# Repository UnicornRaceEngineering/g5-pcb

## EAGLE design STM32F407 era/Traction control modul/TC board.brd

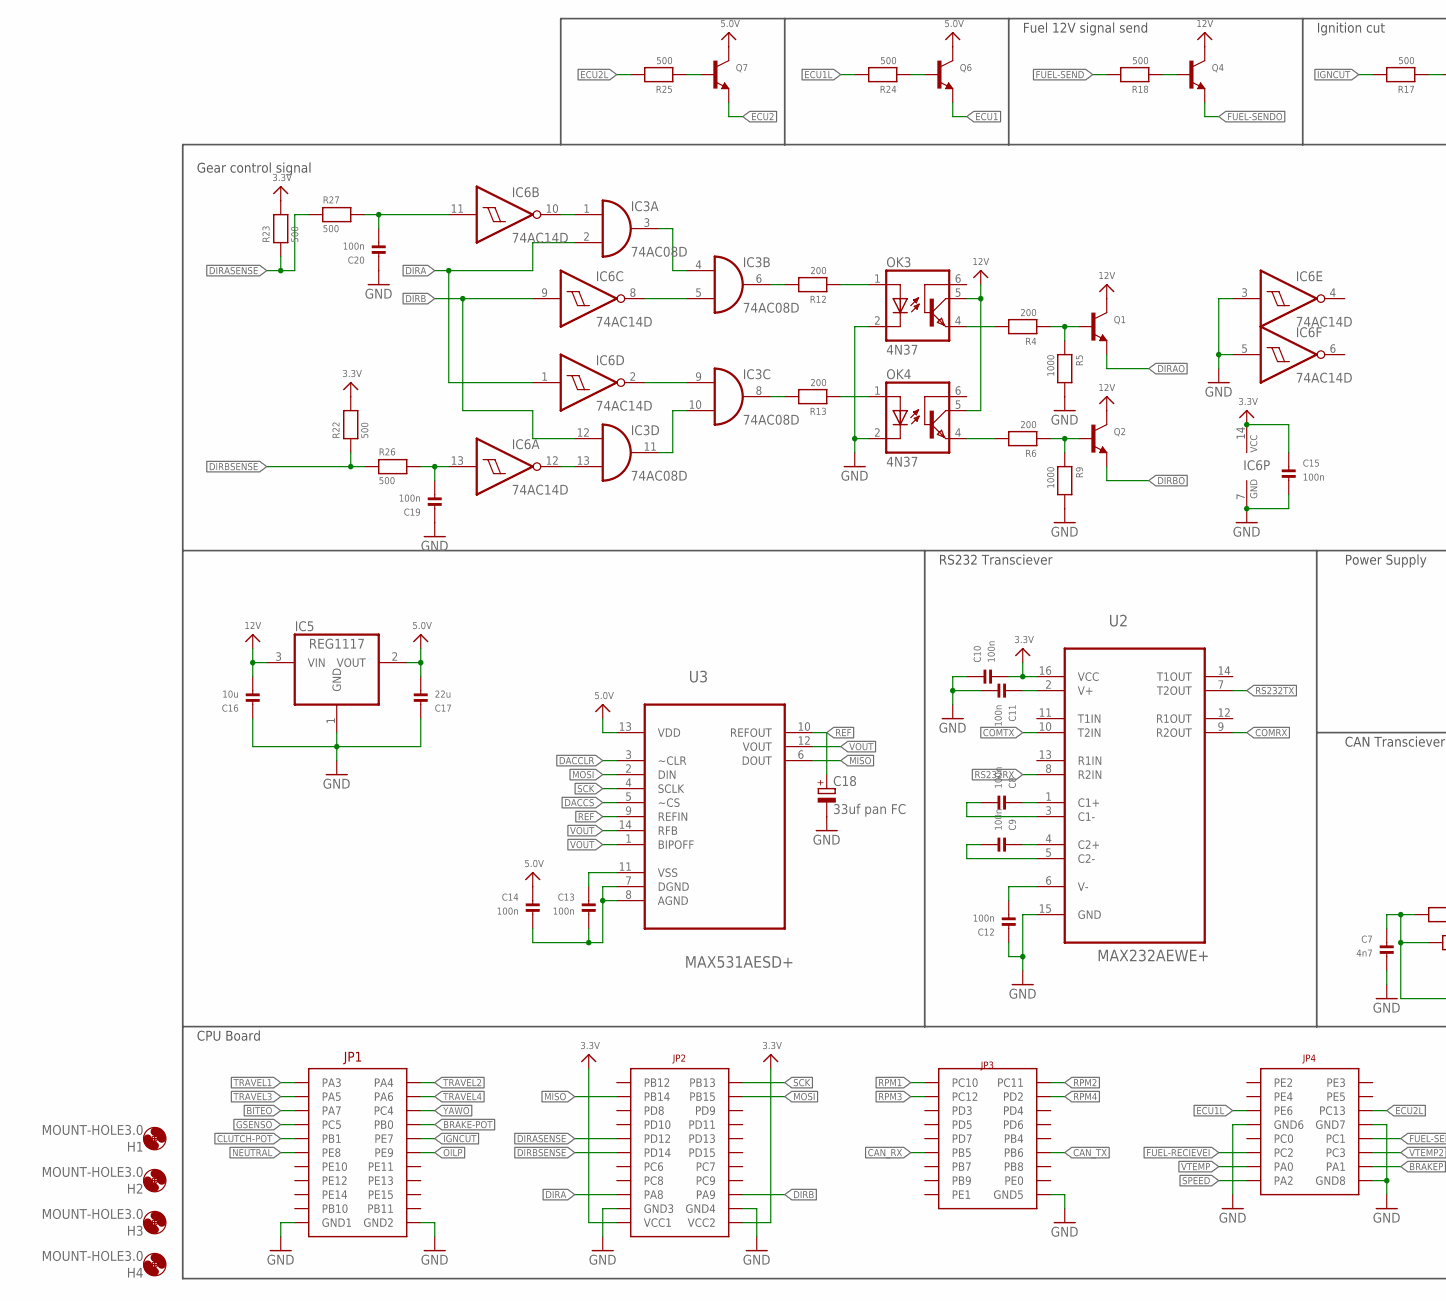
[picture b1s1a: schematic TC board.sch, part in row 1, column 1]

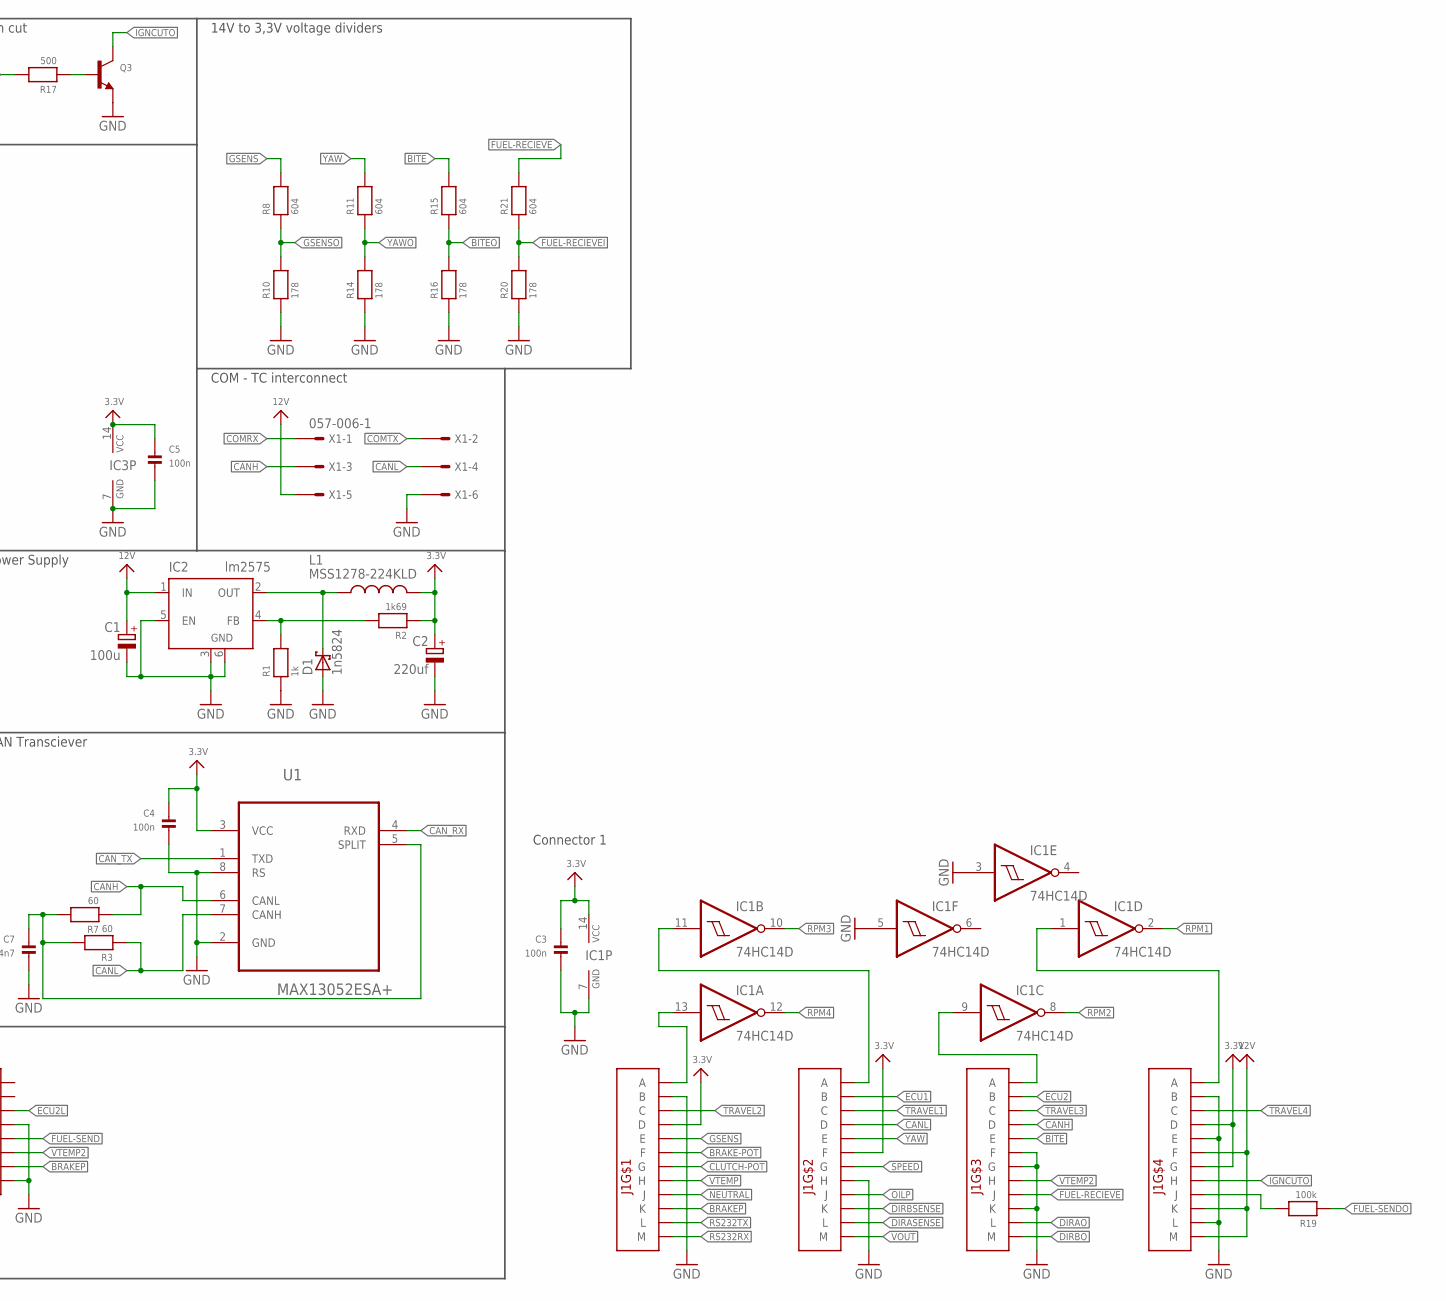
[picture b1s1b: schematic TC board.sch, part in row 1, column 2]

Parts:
C1: 100u; E2,5-7
C2: 220uf; E3,5-8
C3, C4, C5, C8, C9, C10, C11, C12, C13, C14, C15: 100n; _0603
C7: 4n7; _0603
C16: 10u; _0805
C17: 22u; _0805
C18: 33uf pan FC; UD-5X5,8_NICHICON
C19, C20: 100n; _0805
D1: 1n5824; F126Z12
H1, H2, H3, H4: MOUNT-HOLE3.0; 3,0
IC1: 74HC14D; SO14
IC2: lm2575; TO263-5
IC3: 74AC08D; SO14
IC5: REG1117; SOT223
IC6: 74AC14D; SO14
J1: CON1; AUTOCONNECTOR
L1: MSS1278-224KLD; CDRH125
OK3, OK4: 4N37; DIL06
Q1, Q2, Q3, Q4, Q6, Q7: TRANSISTOR_NPNWIDE; SOT23-WIDE
R1: 1k; _0603
R2: 1k69; _0603
R3, R7: 60; _0603
R4, R6, R12, R13: 200; _0603
R5, R9: 1000; _0603
R8, R11, R15, R21: 604; _0603
R10, R14, R16, R20: 178; _0603
R17, R18, R22, R23, R24, R25, R26, R27: 500; _0603
R19: 100k; _0603
U1: MAX13052ESA+; SOIC127P600X175-8N
U2: MAX232AEWE+; SOIC127P1032X265-16N
U3: MAX531AESD+; SOIC127P600X175-14N
U$1: CPU-BOARD; CPU-BOARD-JP1
X1: 057-006-1

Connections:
3.3V: C2.+, C3.1, C4.1, C5.1, C10.2, C15.1, IC1.14 (VCC), IC3.14 (VCC), IC6.14 (VCC), J1.D1 (D), J1.D4 (D), J1.F2 (F), J1.G4 (G), L1.2, R2.1, R22.2, R23.2, U1.3 (VCC), U2.16 (VCC), U$1.P$43 (VCC1), U$1.P$44 (VCC2)
5.0V: C14.1, C17.2, IC5.2 (VOUT), Q6.3 (C), Q7.3 (C), U3.13 (VDD)
12V: C1.+, C16.2, IC2.1 (IN), IC5.3 (VIN), J1.F4 (F), J1.K4 (K), J1.M4 (M), OK3.5 (COL), OK4.5 (COL), Q1.3 (C), Q2.3 (C), Q4.3 (C), X1.5
BITE: J1.E3 (E), R15.2
BITEO: R15.1, R16.2, U$1.P$5 (PA7)
BRAKE-POT: J1.F1 (F), U$1.P$8 (PB0)
BRAKEP: J1.K1 (K), U$1.P$76 (PA1)
CANH: J1.D3 (D), R7.1, U1.6 (CANL), X1.3
CANL: J1.D2 (D), R3.1, U1.7 (CANH), X1.4
CAN_RX: U1.4 (RXD), U$1.P$55 (PB5)
CAN_TX: U1.1 (TXD), U$1.P$56 (PB6)
CLUTCH-POT: J1.G1 (G), U$1.P$9 (PB1)
COMRX: U2.9 (R2OUT), X1.1
COMTX: U2.10 (T2IN), X1.2
DACCLR: U3.3 (~CLR)
DACCS: U3.5 (~CS)
DIRA: IC3.2 (I1), IC6.1 (I), U$1.P$39 (PA8)
DIRAO: J1.L3 (L), Q1.2 (E)
DIRASENSE: J1.L2 (L), R23.1, R27.1, U$1.P$31 (PD12)
DIRB: IC3.12 (I0), IC6.9 (I), U$1.P$40 (PA9)
DIRBO: J1.M3 (M), Q2.2 (E)
DIRBSENSE: J1.K2 (K), R22.1, R26.1, U$1.P$33 (PD14)
ECU1: J1.B2 (B), Q6.2 (E)
ECU1L: R24.2, U$1.P$67 (PE6)
ECU2: J1.B3 (B), Q7.2 (E)
ECU2L: R25.2, U$1.P$68 (PC13)
FUEL-RECIEVE: J1.J3 (J), R21.2
FUEL-RECIEVEI: R20.2, R21.1, U$1.P$73 (PC2)
FUEL-SEND: R18.2, U$1.P$72 (PC1)
FUEL-SENDO: Q4.2 (E), R19.1
GND: C1.-, C2.-, C3.2, C4.2, C5.2, C7.2, C10.1, C11.2, C12.1, C15.2, C16.1, C17.1, C18.-, C19.1, C20.1, D1.A, IC1.3 (I), IC1.5 (I), IC1.7 (GND), IC2.3 (GND), IC2.5 (EN), IC2.6 (GND), IC3.7 (GND), IC5.1 (GND), IC6.3 (I), IC6.5 (I), IC6.7 (GND), J1.B1 (B), J1.B4 (B), J1.E4 (E), J1.F3 (F), J1.G3 (G), J1.H2 (H), J1.K3 (K), J1.L4 (L), OK3.2 (C), OK4.2 (C), Q3.2 (E), R1.1, R5.2, R9.2, R10.1, R14.1, R16.1, R20.1, U1.2 (GND), U1.8 (RS), U2.15 (GND), U$1.P$19 (GND1), U$1.P$20 (GND2), U$1.P$41 (GND3), U$1.P$42 (GND4), U$1.P$62 (GND5), U$1.P$69 (GND6), U$1.P$70 (GND7), U$1.P$78 (GND8), X1.6
GSENS: J1.E1 (E), R8.2
GSENSO: R8.1, R10.2, U$1.P$7 (PC5)
IGNCUT: R17.2, U$1.P$10 (PE7)
IGNCUTO: J1.H4 (H), Q3.3 (C)
MISO: U3.6 (DOUT), U$1.P$25 (PB14)
MOSI: U3.2 (DIN), U$1.P$26 (PB15)
unnamed: IC2.4 (FB), R1.2, R2.2
unnamed: D1.C, IC2.2 (OUT), L1.1
unnamed: IC1.9 (I), J1.A3 (A)
unnamed: IC1.13 (I), J1.A1 (A)
unnamed: IC1.1 (I), J1.A4 (A)
unnamed: IC1.11 (I), J1.A2 (A)
unnamed: OK3.4 (EMI), R4.2
unnamed: Q1.1 (B), R4.1, R5.1
unnamed: OK4.4 (EMI), R6.2
unnamed: Q2.1 (B), R6.1, R9.1
unnamed: IC3.8 (O), R13.2
unnamed: C7.1, R3.2, R7.2, U1.5 (SPLIT)
unnamed: C12.2, U2.6 (V-)
unnamed: C9.1, U2.4 (C2+)
unnamed: IC3.9 (I0), IC6.2 (O)
unnamed: IC3.5 (I1), IC6.8 (O)
unnamed: OK4.1 (A), R13.1
unnamed: OK3.1 (A), R12.1
unnamed: IC3.6 (O), R12.2
unnamed: C9.2, U2.5 (C2-)
unnamed: C8.2, U2.3 (C1-)
unnamed: C8.1, U2.1 (C1+)
unnamed: C11.1, U2.2 (V+)
unnamed: Q3.1 (B), R17.1
unnamed: J1.J4 (J), R19.2
unnamed: Q4.1 (B), R18.1
unnamed: C13.2, C14.2, U3.7 (DGND), U3.8 (AGND)
unnamed: C13.1, U3.11 (VSS)
unnamed: IC3.3 (O), IC3.4 (I0)
unnamed: IC3.10 (I1), IC3.11 (O)
unnamed: IC3.13 (I1), IC6.12 (O)
unnamed: IC3.1 (I0), IC6.10 (O)
unnamed: C20.2, IC6.11 (I), R27.2
unnamed: Q6.1 (B), R24.1
unnamed: Q7.1 (B), R25.1
unnamed: C19.2, IC6.13 (I), R26.2
NEUTRAL: J1.J1 (J), U$1.P$11 (PE8)
OILP: J1.J2 (J), U$1.P$12 (PE9)
REF: C18.+, U3.9 (REFIN), U3.10 (REFOUT)
RPM1: IC1.2 (O), U$1.P$45 (PC10)
RPM2: IC1.8 (O), U$1.P$46 (PC11)
RPM3: IC1.10 (O), U$1.P$47 (PC12)
RPM4: IC1.12 (O), U$1.P$48 (PD2)
RS232RX: J1.M1 (M), U2.8 (R2IN)
RS232TX: J1.L1 (L), U2.7 (T2OUT)
SCK: U3.4 (SCLK), U$1.P$24 (PB13)
SPEED: J1.G2 (G), U$1.P$77 (PA2)
TRAVEL1: J1.C2 (C), U$1.P$1 (PA3)
TRAVEL2: J1.C1 (C), U$1.P$2 (PA4)
TRAVEL3: J1.C3 (C), U$1.P$3 (PA5)
TRAVEL4: J1.C4 (C), U$1.P$4 (PA6)
VOUT: J1.M2 (M), U3.1 (BIPOFF), U3.12 (VOUT), U3.14 (RFB)
VTEMP: J1.H1 (H), U$1.P$75 (PA0)
VTEMP2: J1.H3 (H), U$1.P$74 (PC3)
YAW: J1.E2 (E), R11.2
YAWO: R11.1, R14.2, U$1.P$6 (PC4)

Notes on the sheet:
CPU Board
Connector 1
RS232 Transciever
CAN Transciever
Power Supply
Gear control signal
COM - TC interconnect
14V to 3,3V voltage dividers
Ignition cut
Fuel 12V signal send

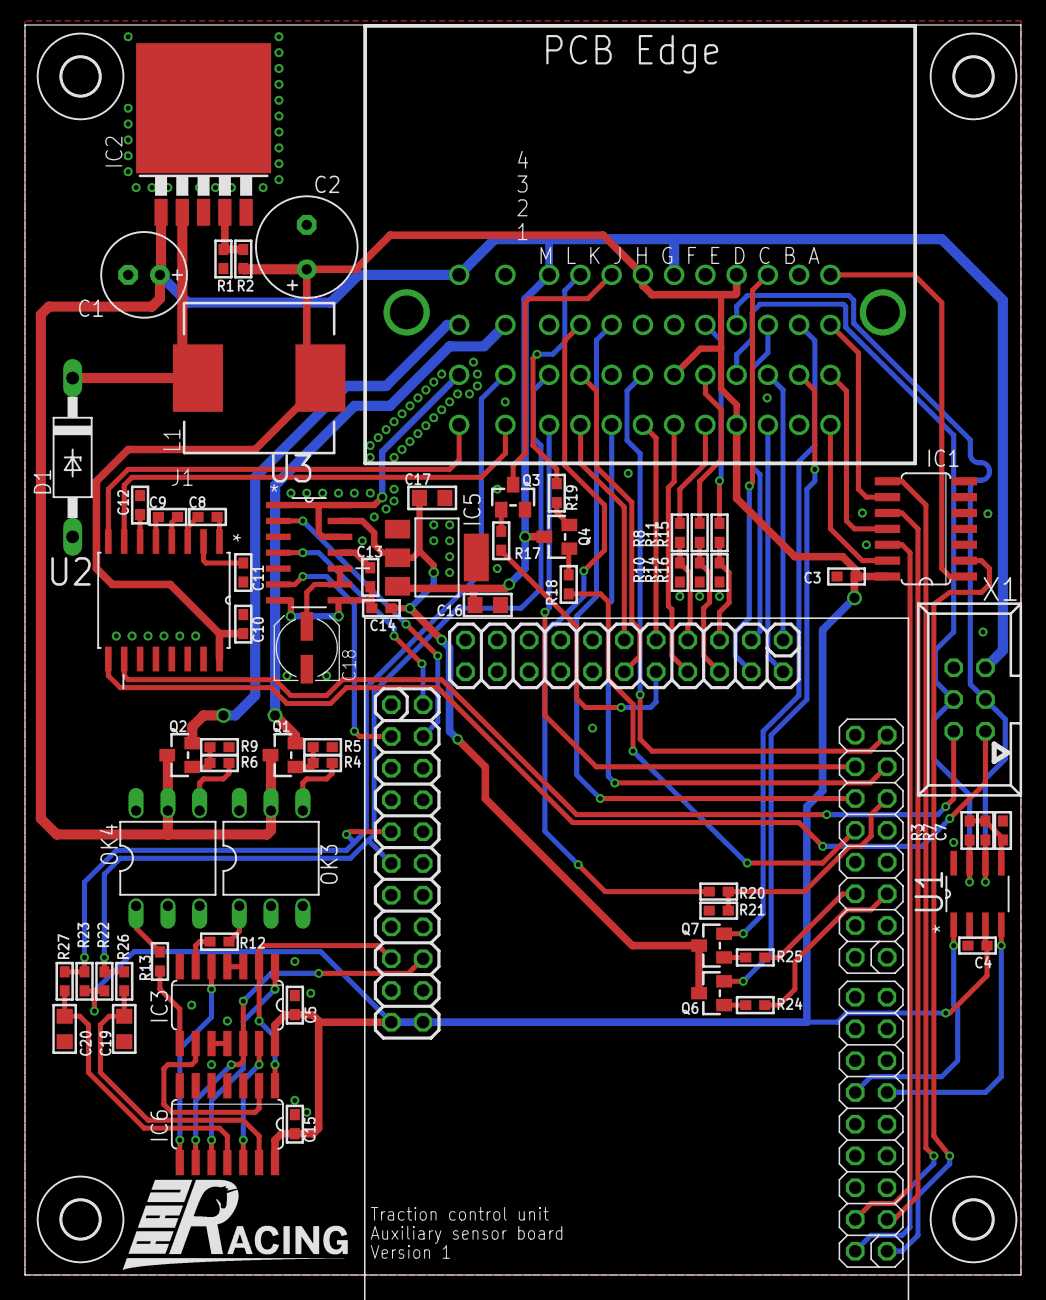
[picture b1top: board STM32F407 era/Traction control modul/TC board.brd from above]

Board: 2 copper layers, 79.7 x 100.0 mm, 71 parts (0 on the bottom side), 91 nets.

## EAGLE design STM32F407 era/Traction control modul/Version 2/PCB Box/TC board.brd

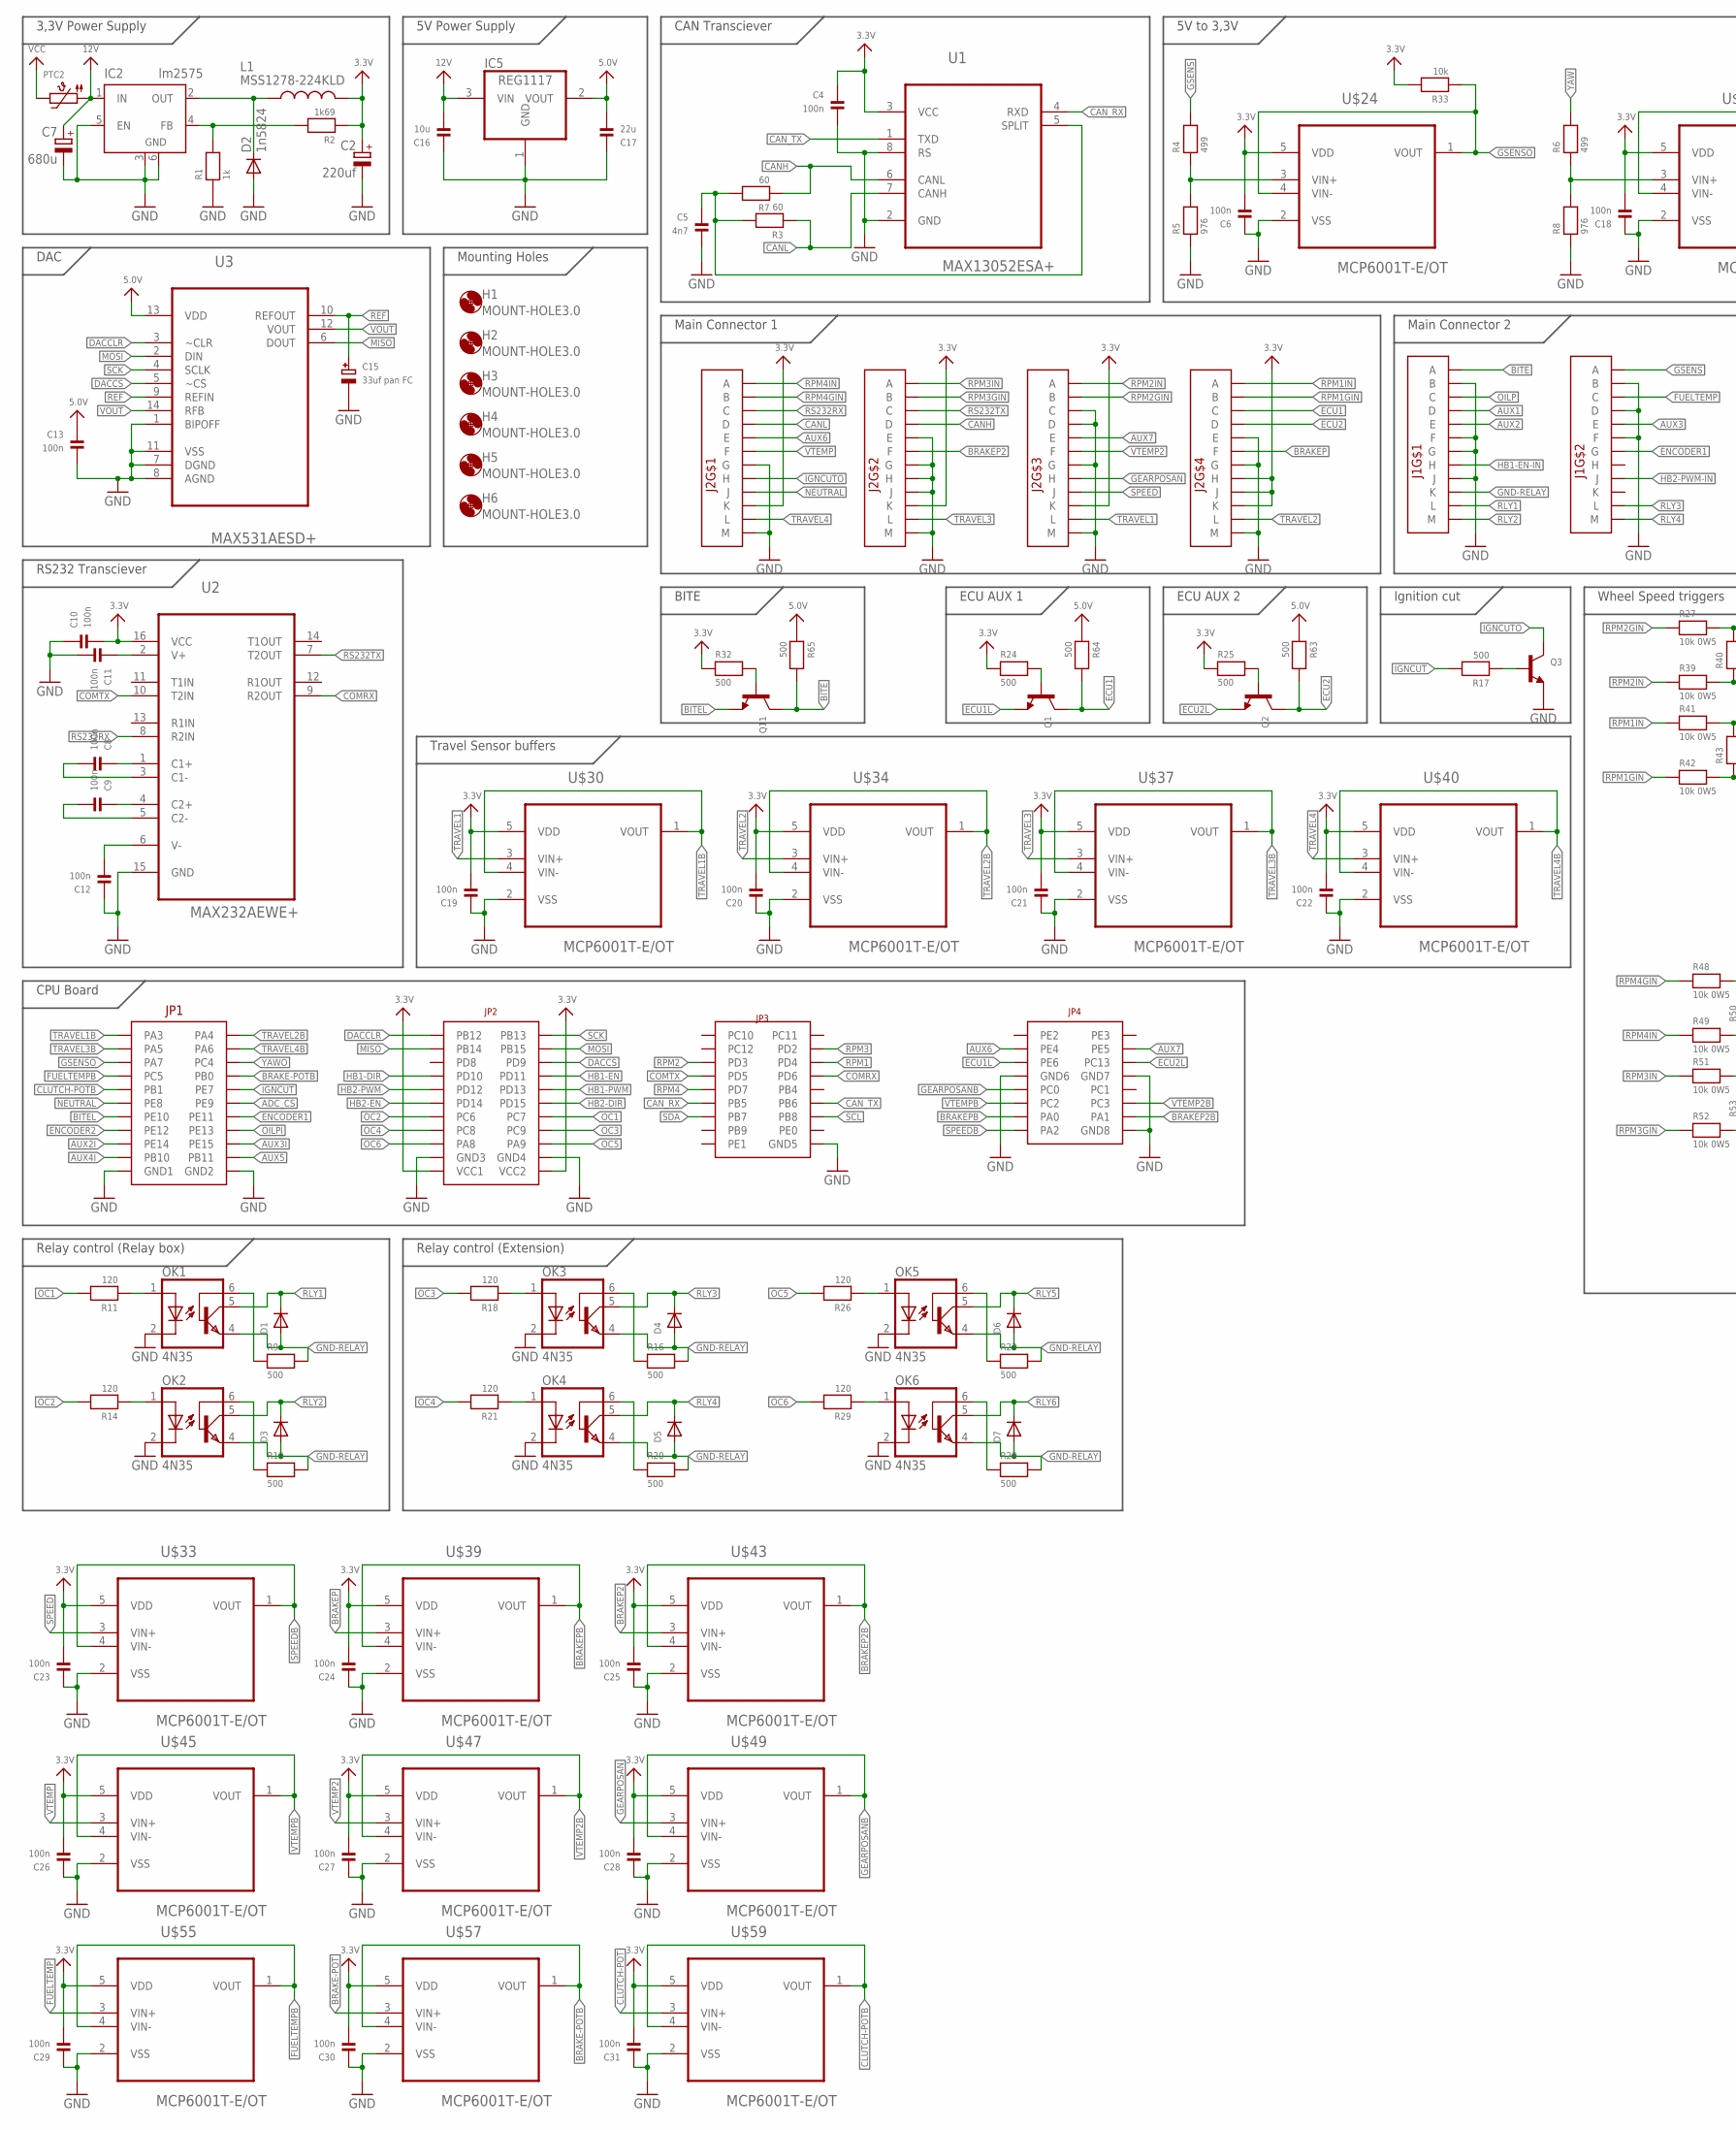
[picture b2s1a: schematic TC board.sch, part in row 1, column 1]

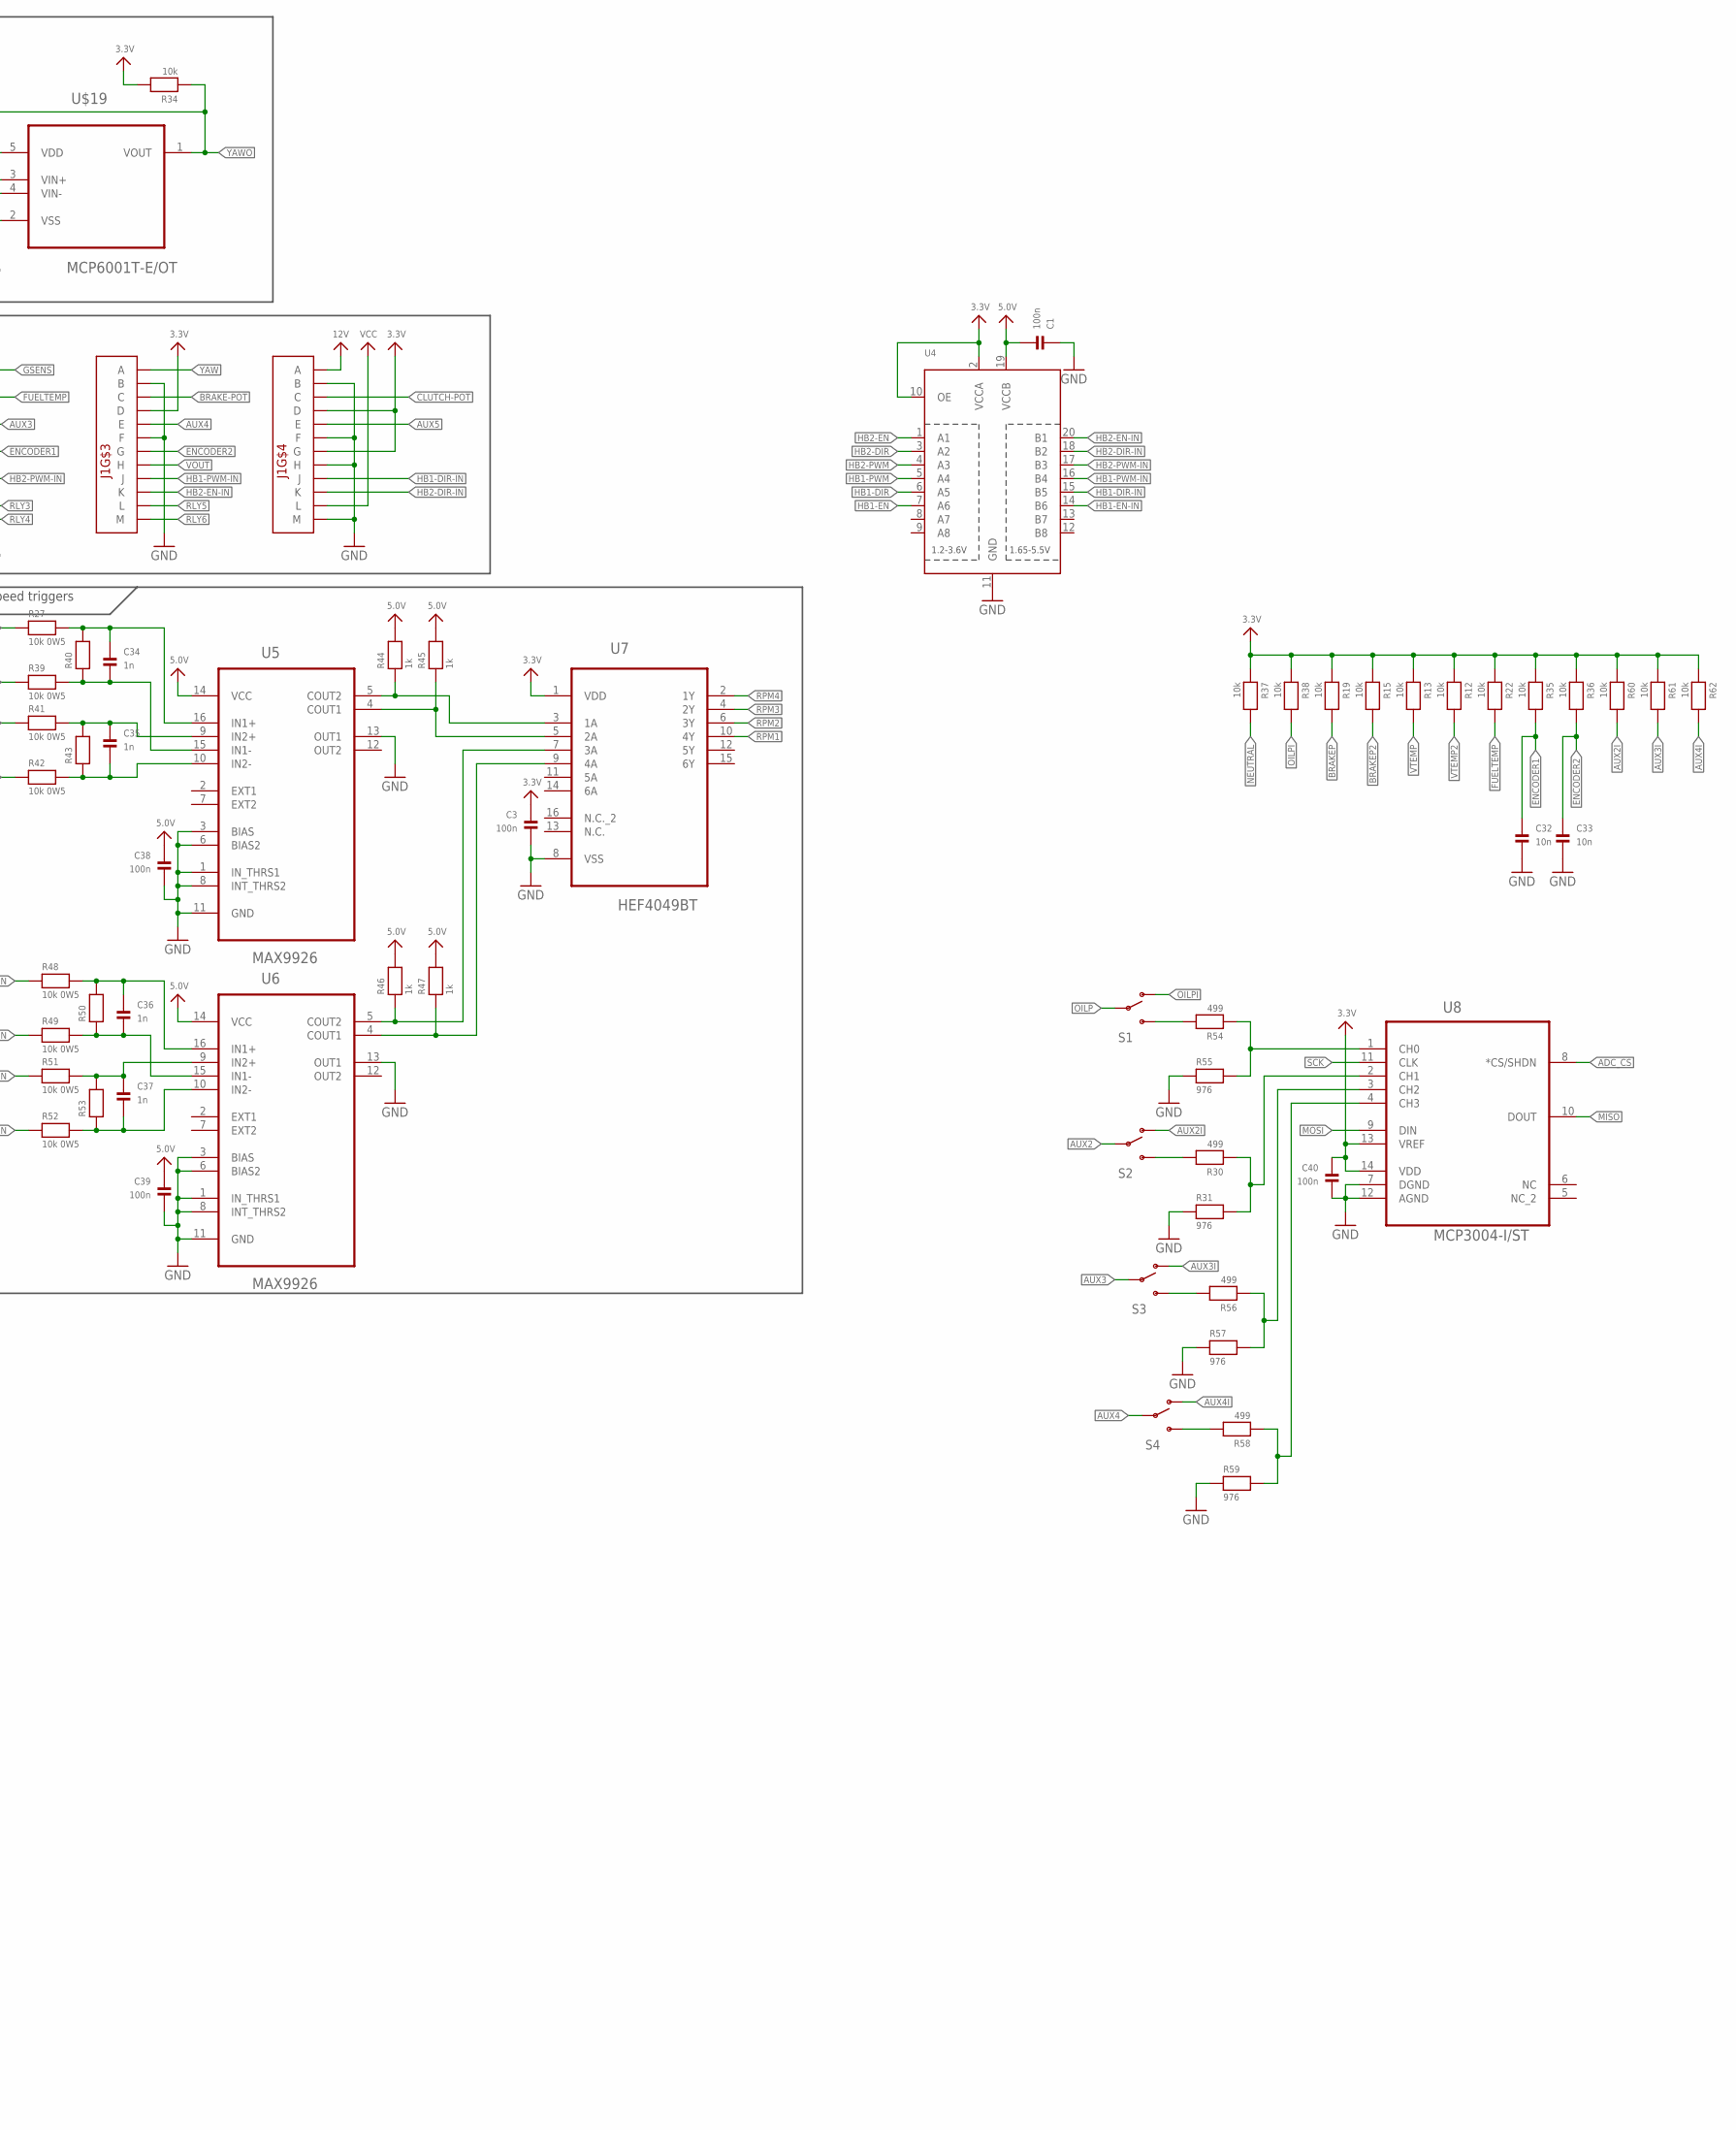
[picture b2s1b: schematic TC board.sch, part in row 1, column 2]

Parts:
C1, C3, C4, C6, C8, C9, C10, C11, C12, C13, C18, C19, C20, C21, C22, C23, C24, C25, C26, C27, C28, C29, C30, C31, C38, C39, C40: 100n; _0603
C2: 220uf; E3,5-8
C5: 4n7; _0603
C7: 680u; E5-10,5
C15: 33uf pan FC; PANASONIC_D
C16: 10u; _0805
C17: 22u; _0805
C32, C33: 10n; _0603
C34, C35, C36, C37: 1n; _0603
D1, D3, D4, D5, D6, D7: DIODESOD-323F; SOD-323F
D2: 1n5824; DO201-15
H1, H2, H3, H4, H5, H6: MOUNT-HOLE3.0; 3,0
IC2: lm2575; TO263-5
IC5: REG1117; SOT223
J1, J2: CON1; AUTOCONNECTOR
L1: MSS1278-224KLD; CDRH125
OK1, OK2, OK3, OK4, OK5, OK6: 4N35; DIL06
PTC2: PTC1812
Q1, Q2, Q3, Q11: TRANSISTOR_NPNWIDE; SOT23-WIDE
R1, R44, R45, R46, R47: 1k; _0603
R2: 1k69; _0603
R3, R7: 60; _0603
R4, R6, R30, R54, R56, R58: 499; _0603
R5, R8, R31, R55, R57, R59: 976; _0603
R9, R10, R16, R17, R20, R23, R24, R25, R28, R32, R63, R64, R65: 500; _0603
R11, R14, R18, R21, R26, R29: 120; _0603
R12, R13, R15, R19, R22, R33, R34, R35, R36, R37, R38, R60, R61, R62: 10k; _0603
R27, R39, R41, R42, R48, R49, R51, R52: 10k 0W5; _0805
R40, R43, R50, R53: RESISTOR_0805; _0805
S1, S2, S3, S4: SWITCH-SPDT-SMD-A; SWITCH-SPST-SMD-A
U1: MAX13052ESA+; SOIC127P600X175-8N
U2: MAX232AEWE+; SOIC127P1032X265-16N
U3: MAX531AESD+; SOIC127P600X175-14N
U4: TXB0108PWR; TSSOP20
U5, U6: MAX9926; SOP63P600X175-16N
U7: HEF4049BT; SOIC127P600X175-16N
U8: MCP3004-I/ST; SOP65P640X120-14N
U$1: CPU-BOARD; CPU-BOARD-JP1
U$19, U$24, U$30, U$33, U$34, U$37, U$39, U$40, U$43, U$45, U$47, U$49, U$55, U$57, U$59: MCP6001T-E/OT; SOT95P270X145-5N

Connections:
3.3V: C2.+, C3.1, C4.1, C6.2, C10.2, C18.2, C19.2, C20.2, C21.2, C22.2, C23.2, C24.2, C25.2, C26.2, C27.2, C28.2, C29.2, C30.2, C31.2, C40.1, J1.D3 (D), J1.D4 (D), J1.G4 (G), J2.H4 (H), J2.J4 (J), J2.K1 (K), J2.K2 (K), J2.K3 (K), J2.K4 (K), L1.2, R2.1, R12.1, R13.1, R15.1, R19.1, R22.1, R24.1, R25.1, R32.1, R33.2, R34.2, R35.1, R36.1, R37.1, R38.1, R60.1, R61.1, R62.1, U1.3 (VCC), U2.16 (VCC), U4.2 (VCCA), U4.10 (OE), U7.1 (VDD), U8.13 (VREF), U8.14 (VDD), U$1.P$43 (VCC1), U$1.P$44 (VCC2), U$19.5 (VDD), U$24.5 (VDD), U$30.5 (VDD), U$33.5 (VDD), U$34.5 (VDD), U$37.5 (VDD), U$39.5 (VDD), U$40.5 (VDD), U$43.5 (VDD), U$45.5 (VDD), U$47.5 (VDD), U$49.5 (VDD), U$55.5 (VDD), U$57.5 (VDD), U$59.5 (VDD)
5.0V: C1.2, C13.1, C17.2, C38.1, C39.1, IC5.2 (VOUT), R44.2, R45.2, R46.2, R47.2, R63.1, R64.1, R65.1, U3.13 (VDD), U4.19 (VCCB), U5.14 (VCC), U6.14 (VCC); also elsewhere on the board
12V: C7.+, C16.2, IC2.1 (IN), IC5.3 (VIN), J1.A4 (A), PTC2.P$1 (1)
ADC_CS: U8.8 (*CS/SHDN), U$1.P$12 (PE9)
AUX1: J1.D1 (D)
AUX2: J1.E1 (E), S2.2
AUX2I: R60.2, S2.1 (O), U$1.P$17 (PE14)
AUX3: J1.E2 (E), S3.2
AUX3I: R61.2, S3.1 (O), U$1.P$18 (PE15)
AUX4: J1.E3 (E), S4.2
AUX4I: R62.2, S4.1 (O), U$1.P$21 (PB10)
AUX5: J1.E4 (E), U$1.P$22 (PB11)
AUX6: J2.E1 (E), U$1.P$65 (PE4)
AUX7: J2.E3 (E), U$1.P$66 (PE5)
BITE: J1.A1 (A), Q11.3 (C), R65.2
BITEL: Q11.2 (E), U$1.P$13 (PE10)
BRAKE-POT: J1.C3 (C), U$57.3 (VIN+)
BRAKE-POTB: U$1.P$8 (PB0), U$57.1 (VOUT), U$57.4 (VIN-)
BRAKEP: J2.F4 (F), R19.2, U$39.3 (VIN+)
BRAKEP2: J2.F2 (F), R15.2, U$43.3 (VIN+)
BRAKEP2B: U$1.P$76 (PA1), U$43.1 (VOUT), U$43.4 (VIN-)
BRAKEPB: U$1.P$75 (PA0), U$39.1 (VOUT), U$39.4 (VIN-)
CANH: J2.D2 (D), R7.1, U1.6 (CANL)
CANL: J2.D1 (D), R3.1, U1.7 (CANH)
CAN_RX: U1.4 (RXD), U$1.P$55 (PB5)
CAN_TX: U1.1 (TXD), U$1.P$56 (PB6)
CLUTCH-POT: J1.C4 (C), U$59.3 (VIN+)
CLUTCH-POTB: U$1.P$9 (PB1), U$59.1 (VOUT), U$59.4 (VIN-)
COMRX: U2.9 (R2OUT), U$1.P$52 (PD6)
COMTX: U2.10 (T2IN), U$1.P$51 (PD5)
DACCLR: U3.3 (~CLR), U$1.P$23 (PB12); also elsewhere on the board
DACCS: U3.5 (~CS), U$1.P$28 (PD9); also elsewhere on the board
ECU1: J2.C4 (C), Q1.3 (C), R64.2
ECU1L: Q1.2 (E), U$1.P$67 (PE6)
ECU2: J2.D4 (D), Q2.3 (C), R63.2
ECU2L: Q2.2 (E), U$1.P$68 (PC13)
ENCODER1: C32.1, J1.G2 (G), R35.2, U$1.P$14 (PE11)
ENCODER2: C33.1, J1.G3 (G), R36.2, U$1.P$15 (PE12)
FUELTEMP: J1.C2 (C), R22.2, U$55.3 (VIN+)
FUELTEMPB: U$1.P$7 (PC5), U$55.1 (VOUT), U$55.4 (VIN-)
GEARPOSAN: J2.H3 (H), U$49.3 (VIN+)
GEARPOSANB: U$1.P$71 (PC0), U$49.1 (VOUT), U$49.4 (VIN-)
GND: C1.1, C2.-, C3.2, C4.2, C5.2, C6.1, C7.-, C10.1, C11.2, C12.1, C13.2, C15.-, C16.1, C17.1, C18.1, C19.1, C20.1, C21.1, C22.1, C23.1, C24.1, C25.1, C26.1, C27.1, C28.1, C29.1, C30.1, C31.1, C32.2, C33.2, C38.2, C39.2, C40.2, D2.A, IC2.3 (GND), IC2.5 (EN), IC2.6 (GND), IC5.1 (GND), J1.B1 (B), J1.B2 (B), J1.B3 (B), J1.B4 (B), J1.D2 (D), J1.F1 (F), J1.F2 (F), J1.F3 (F), J1.F4 (F), J1.G1 (G), J1.H4 (H), J1.J1 (J), J1.M4 (M), J2.C3 (C), J2.D3 (D), J2.E2 (E), J2.E4 (E), J2.G1 (G), J2.G2 (G), J2.G3 (G), J2.G4 (G), J2.H2 (H), J2.J2 (J), J2.M1 (M), J2.M2 (M), J2.M3 (M), J2.M4 (M), OK1.2 (C), OK2.2 (C), OK3.2 (C), OK4.2 (C), OK5.2 (C), OK6.2 (C), Q3.2 (E), R1.1, R5.1, R8.1, R31.1, R55.1, R57.1, R59.1, U1.2 (GND), U1.8 (RS), U2.15 (GND), U3.1 (BIPOFF), U3.7 (DGND), U3.8 (AGND), U3.11 (VSS), U4.11 (GND), U5.1 (IN_THRS1), U5.3 (BIAS), U5.6 (BIAS2), U5.8 (INT_THRS2), U5.11 (GND), U5.13 (OUT1), U6.1 (IN_THRS1), U6.3 (BIAS), U6.6 (BIAS2), U6.8 (INT_THRS2), U6.11 (GND), U6.13 (OUT1), U7.8 (VSS), U8.7 (DGND), U8.12 (AGND), U$1.P$19 (GND1), U$1.P$20 (GND2), U$1.P$41 (GND3), U$1.P$42 (GND4), U$1.P$62 (GND5), U$1.P$69 (GND6), U$1.P$70 (GND7), U$1.P$78 (GND8), U$19.2 (VSS), U$24.2 (VSS), U$30.2 (VSS), U$33.2 (VSS), U$34.2 (VSS), U$37.2 (VSS), U$39.2 (VSS), U$40.2 (VSS), U$43.2 (VSS), U$45.2 (VSS), U$47.2 (VSS), U$49.2 (VSS), U$55.2 (VSS), U$57.2 (VSS), U$59.2 (VSS); also elsewhere on the board
GND-RELAY: D1.A, D3.A, D4.A, D5.A, D6.A, D7.A, J1.K1 (K), OK1.4 (EMI), OK2.4 (EMI), OK3.4 (EMI), OK4.4 (EMI), OK5.4 (EMI), OK6.4 (EMI), R9.2, R10.2, R16.2, R20.2, R23.2, R28.2
GSENS: J1.A2 (A), R4.2
GSENSO: R33.1, U$1.P$5 (PA7), U$24.1 (VOUT), U$24.4 (VIN-)
HB1-DIR: U4.6 (A5), U$1.P$29 (PD10)
HB1-DIR-IN: J1.J4 (J), U4.15 (B5)
HB1-EN: U4.7 (A6), U$1.P$30 (PD11)
HB1-EN-IN: J1.H1 (H), U4.14 (B6)
HB1-PWM: U4.5 (A4), U$1.P$32 (PD13)
HB1-PWM-IN: J1.J3 (J), U4.16 (B4)
HB2-DIR: U4.3 (A2), U$1.P$34 (PD15)
HB2-DIR-IN: J1.K4 (K), U4.18 (B2)
HB2-EN: U4.1 (A1), U$1.P$33 (PD14)
HB2-EN-IN: J1.K3 (K), U4.20 (B1)
HB2-PWM: U4.4 (A3), U$1.P$31 (PD12)
HB2-PWM-IN: J1.J2 (J), U4.17 (B3)
IGNCUT: R17.2, U$1.P$10 (PE7)
IGNCUTO: J2.H1 (H), Q3.3 (C)
MISO: U3.6 (DOUT), U8.10 (DOUT), U$1.P$25 (PB14)
MOSI: U3.2 (DIN), U8.9 (DIN), U$1.P$26 (PB15); also elsewhere on the board
unnamed: IC2.4 (FB), R1.2, R2.2
unnamed: D2.C, IC2.2 (OUT), L1.1
unnamed: OK1.6 (BAS), R9.1
unnamed: Q11.1 (B), R32.2
unnamed: OK3.6 (BAS), R16.1
unnamed: OK1.1 (A), R11.1
unnamed: R4.1, R5.2, U$24.3 (VIN+)
unnamed: OK4.6 (BAS), R20.1
unnamed: OK2.6 (BAS), R10.1
unnamed: OK2.1 (A), R14.1
unnamed: C34.1, R27.2, R40.2, U5.16 (IN1+)
unnamed: C5.1, R3.2, R7.2, U1.5 (SPLIT)
unnamed: C12.2, U2.6 (V-)
unnamed: C9.1, U2.4 (C2+)
unnamed: C34.2, R39.2, R40.1, U5.15 (IN1-)
unnamed: OK3.1 (A), R18.1
unnamed: C35.1, R41.2, R43.2, U5.9 (IN2+)
unnamed: C35.2, R42.2, R43.1, U5.10 (IN2-)
unnamed: OK4.1 (A), R21.1
unnamed: C9.2, U2.5 (C2-)
unnamed: C8.2, U2.3 (C1-)
unnamed: C8.1, U2.1 (C1+)
unnamed: C11.1, U2.2 (V+)
unnamed: Q3.1 (B), R17.1
unnamed: OK5.6 (BAS), R23.1
unnamed: OK6.6 (BAS), R28.1
unnamed: OK5.1 (A), R26.1
unnamed: R44.1, U5.5 (COUT2), U7.3 (1A)
unnamed: R46.1, U6.5 (COUT2), U7.7 (3A)
unnamed: R30.2, S2.3 (S)
unnamed: R45.1, U5.4 (COUT1), U7.5 (2A)
unnamed: R6.1, R8.2, U$19.3 (VIN+)
unnamed: R47.1, U6.4 (COUT1), U7.9 (4A)
unnamed: Q1.1 (B), R24.2
unnamed: Q2.1 (B), R25.2
unnamed: C36.1, R48.2, R50.2, U6.16 (IN1+)
unnamed: OK6.1 (A), R29.1
unnamed: C37.1, R51.2, R53.2, U6.9 (IN2+)
unnamed: C37.2, R52.2, R53.1, U6.10 (IN2-)
unnamed: C36.2, R49.2, R50.1, U6.15 (IN1-)
unnamed: R54.1, R55.2, U8.1 (CH0)
unnamed: R30.1, R31.2, U8.2 (CH1)
unnamed: R56.2, S3.3 (S)
unnamed: R56.1, R57.2, U8.3 (CH2)
unnamed: R54.2, S1.3 (S)
unnamed: R58.2, S4.3 (S)
unnamed: R58.1, R59.2, U8.4 (CH3)
NEUTRAL: J2.J1 (J), R37.2, U$1.P$11 (PE8)
unnamed: C15.+, U3.9 (REFIN), U3.10 (REFOUT)
OC1: R11.2, U$1.P$36 (PC7)
OC2: R14.2, U$1.P$35 (PC6)
OC3: R18.2, U$1.P$38 (PC9)
OC4: R21.2, U$1.P$37 (PC8)
OC5: R26.2, U$1.P$40 (PA9)
OC6: R29.2, U$1.P$39 (PA8)
OILP: J1.C1 (C), S1.2
OILPI: R38.2, S1.1 (O), U$1.P$16 (PE13)
RLY1: D1.C, J1.L1 (L), OK1.5 (COL)
RLY2: D3.C, J1.M1 (M), OK2.5 (COL)
RLY3: D4.C, J1.L2 (L), OK3.5 (COL)
RLY4: D5.C, J1.M2 (M), OK4.5 (COL)
RLY5: D6.C, J1.L3 (L), OK5.5 (COL)
RLY6: D7.C, J1.M3 (M), OK6.5 (COL)
RPM1: U7.10 (4Y), U$1.P$50 (PD4)
RPM1GIN: J2.B4 (B), R42.1
RPM1IN: J2.A4 (A), R41.1
RPM2: U7.6 (3Y), U$1.P$49 (PD3)
RPM2GIN: J2.B3 (B), R27.1
RPM2IN: J2.A3 (A), R39.1
RPM3: U7.4 (2Y), U$1.P$48 (PD2)
RPM3GIN: J2.B2 (B), R52.1
RPM3IN: J2.A2 (A), R51.1
RPM4: U7.2 (1Y), U$1.P$53 (PD7)
RPM4GIN: J2.B1 (B), R48.1
RPM4IN: J2.A1 (A), R49.1
RS232RX: J2.C1 (C), U2.8 (R2IN)
RS232TX: J2.C2 (C), U2.7 (T2OUT)
SCK: U3.4 (SCLK), U8.11 (CLK), U$1.P$24 (PB13); also elsewhere on the board
SCL: U$1.P$58 (PB8)
SDA: U$1.P$57 (PB7)
SPEED: J2.J3 (J), U$33.3 (VIN+)
SPEEDB: U$1.P$77 (PA2), U$33.1 (VOUT), U$33.4 (VIN-)
TRAVEL1: J2.L3 (L), U$30.3 (VIN+)
TRAVEL1B: U$1.P$1 (PA3), U$30.1 (VOUT), U$30.4 (VIN-)
TRAVEL2: J2.L4 (L), U$34.3 (VIN+)
TRAVEL2B: U$1.P$2 (PA4), U$34.1 (VOUT), U$34.4 (VIN-)
TRAVEL3: J2.L2 (L), U$37.3 (VIN+)
TRAVEL3B: U$1.P$3 (PA5), U$37.1 (VOUT), U$37.4 (VIN-)
TRAVEL4: J2.L1 (L), U$40.3 (VIN+)
TRAVEL4B: U$1.P$4 (PA6), U$40.1 (VOUT), U$40.4 (VIN-)
VCC: J1.L4 (L), PTC2.P$2 (2)
VOUT: J1.H3 (H), U3.12 (VOUT), U3.14 (RFB); also elsewhere on the board
VTEMP: J2.F1 (F), R13.2, U$45.3 (VIN+)
VTEMP2: J2.F3 (F), R12.2, U$47.3 (VIN+)
VTEMP2B: U$1.P$74 (PC3), U$47.1 (VOUT), U$47.4 (VIN-)
VTEMPB: U$1.P$73 (PC2), U$45.1 (VOUT), U$45.4 (VIN-)
YAW: J1.A3 (A), R6.2
YAWO: R34.1, U$1.P$6 (PC4), U$19.1 (VOUT), U$19.4 (VIN-)

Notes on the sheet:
CPU Board
RS232 Transciever
CAN Transciever
5V to 3,3V
Ignition cut
DAC
3,3V Power Supply
5V Power Supply
Mounting Holes
ECU AUX 1
ECU AUX 2
Wheel Speed triggers
Main Connector 1
Main Connector 2
Relay control (Relay box)
Relay control (Extension)
BITE
Travel Sensor buffers

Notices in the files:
parts and their libraries:
microbuilder: This work is placed in the public domain, and may be freely used for commercial and non-commercial work with the following conditions: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
SparkFun-Passives: Licensing: Creative Commons ShareAlike 4.0 International - https://creativecommons.org/licenses/by-sa/4.0
